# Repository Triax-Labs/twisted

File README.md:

<h1 align="center">Twisted</h1>

Twisted is a tiny (14x32mm to be precise) ESP32-S3 based platform, which has dual Xtensa LX7 cores, 4Mb of flash, 2Mb of PSRAM, 512Kb of SRAM as well as BLE and WiFi on board, paired with an [0.42" IPS LCD](https://www.buydisplay.com/0-42-inch-mini-color-tft-lcd-display-module-96x54-ips-st7735), a keypad, a Neopixel and built-in battery management with USB OTG.

There is one more thing, the platform is extendable! It features a 20 pin 1.27mm expansion header which allows you of attaching other boards that add extra features, giving _Twisted_ a reason for its name.

We currently have three expansion boards for Twisted...

## Twisted Listen

An audio codec based on ES8316, which provides a high performance DAC and ADC, the attachment comes with both a builtin microphone and amplifier for a loudspeaker, as well as a 3.5mm headphone jack (with microphone in.)

## Twisted Connect

A shield for the Twisted Bus that provides the functionality of an extra microcontroller, it adds on a CH585 MCU which comes with an interesting set of peripherals, NFC/RFID (with support for reading, writing and emulating tags,) both a USB High Speed and a USB Full Speed controller as well as a BLE / 2.4GHz modem.

Twisted Connect could be used for using the peripherals on the CH585 MCU alongside the ESP32-S3 on the main Twisted board or it could be used to deep sleep the ESP32-S3 to preserve power, since Twisted Connect could take over the bus, it can wake up the ESP32-S3 when a trigger happens (e.g. sensors over I2C or a BLE/USB packet.)

## Twisted Sense (WIP)

An attachment that provides a a suite of sensors and trackers (pressure, temperature, humidity, gyroscope, accelerometer, magnetometer and GPS/GNSS) aiming to help the device "feel" what happens around it.

## Production

Production could be done through [JLCPCB](https://jlcpcb.com)'s PCBA service.

Total _(estimated)_ costs for Twisted boards (does not include any of the extra shields):

| Item | Price | Qty      | Where                        |
| ---- | ----- | -------- | ---------------------------- |
| PCB  | $7    | 5 Boards | [JLCPCB](https://jlcpcb.com) |
| PCBA | $100  | 5 Boards | [JLCPCB](https://jlcpcb.com) |

You will need to assemble one side of the board, the other side which has the display, a resistor and the keypad you will have to assemble it yourself, or let JLCPCB assemble it for you at a higher cost.

You will need the display to be sourced and assembled by yourself, this is where you can buy it:

- AliExpress: [listing](https://aliexpress.com/item/1005007804650049.html) / [listing](https://aliexpress.com/item/1005008528322628.html) / [listing](https://aliexpress.com/item/1005012246832580.html) / [listing](https://aliexpress.com/item/1005008885821582.html)
- [BuyDisplay](https://www.buydisplay.com/0-42-inch-mini-color-tft-lcd-display-module-96x54-ips-st7735)

If you decide to buy the display from a different supplier, make sure it comes with a 16 pin flex cable, it also has to follow this pinout:

Total _(estimated)_ costs for Twisted Listen boards:

| Item | Price | Qty      | Where                        |
| ---- | ----- | -------- | ---------------------------- |
| PCB  | $7    | 5 Boards | [JLCPCB](https://jlcpcb.com) |
| PCBA | $60   | 5 Boards | [JLCPCB](https://jlcpcb.com) |

Total _(estimated)_ costs for a Twisted Connect boards:

| Item | Price | Qty      | Where                        |
| ---- | ----- | -------- | ---------------------------- |
| PCB  | $7    | 5 Boards | [JLCPCB](https://jlcpcb.com) |
| PCBA | $80   | 5 Boards | [JLCPCB](https://jlcpcb.com) |

_Note that these tables don't include shipping charges._

Production files could be found in `/hardware/X/production`.

## GPIO Pins Mapping (Twisted Bus)

| GPIO | Strap |   ADC    | HWSPI | Remark                                              |      Exposed      | On Twisted        |
| :--: | :---: | :------: | :---: | --------------------------------------------------- | :---------------: | ----------------- |
|  0   |  Yes  |          |       | Pull LOW to Enter BOOT                              |        No         | Boot Button       |
|  1   |  No   | ADC1 CH0 |       |                                                     |        Yes        | Expansion Header  |
|  2   |  No   | ADC1 CH1 |       |                                                     |        Yes        | Expansion Header  |
|  3   |  Yes  | ADC1 CH2 |       | Pull LOW to Use An External Debugger Instead of USB |        Yes        | Expansion Header  |
|  4   |  No   | ADC1 CH3 |       |                                                     |        Yes        | Expansion Header  |
|  5   |  No   | ADC1 CH4 |       |                                                     |        Yes        | Expansion Header  |
|  6   |  No   | ADC1 CH5 |       |                                                     |        Yes        | Expansion Header  |
|  7   |  No   | ADC1 CH6 |       |                                                     |        Yes        | Expansion Header  |
|  8   |  No   | ADC1 CH7 |       |                                                     |        Yes        | Expansion Header  |
|  9   |  No   | ADC1 CH8 | Hold  |                                                     |        Yes        | Expansion Header  |
|  10  |  No   | ADC1 CH9 |  CS   |                                                     |        Yes        | Expansion Header  |
|  11  |  No   | ADC2 CH0 | MOSI  |                                                     |        Yes        | Expansion Header  |
|  12  |  No   | ADC2 CH1 |  SCK  |                                                     |        Yes        | Expansion Header  |
|  13  |  No   | ADC2 CH2 | MISO  |                                                     |        Yes        | Expansion Header  |
|  14  |  No   | ADC2 CH3 |  WP   |                                                     |        Yes        | Expansion Header  |
|  15  |  No   | ADC2 CH4 |       |                                                     |        Yes        | Expansion Header  |
|  16  |  No   | ADC2 CH5 |       |                                                     |        Yes        | Expansion Header  |
|  17  |  No   | ADC2 CH6 |       |                                                     |        Yes        | Expansion Header  |
|  18  |  No   | ADC2 CH7 |       |                                                     |        No         | Keypad: INT       |
|  19  |  Yes  | ADC2 CH8 |       | USB D-                                              |        Yes        | USB Port          |
|  20  |  Yes  | ADC2 CH9 |       | USB D+                                              |        Yes        | USB Port          |
|  21  |  No   |          |       |                                                     |        No         | Neopixel: DIN     |
|  26  |  Yes  |          |       | Used for QSPI Flash/PSRAM                           |        No         | Unused            |
|  27  |  Yes  |          |       | Used for QSPI Flash/PSRAM                           |        No         | Unused            |
|  28  |  Yes  |          |       | Used for QSPI Flash/PSRAM                           |        No         | Unused            |
|  29  |  Yes  |          |       | Used for QSPI Flash/PSRAM                           |        No         | Unused            |
|  30  |  Yes  |          |       | Used for QSPI Flash/PSRAM                           |        No         | Unused            |
|  31  |  Yes  |          |       | Used for QSPI Flash/PSRAM                           |        No         | Unused            |
|  32  |  Yes  |          |       | Used for QSPI Flash/PSRAM                           |        No         | Unused            |
|  33  | Maybe |          |       | Straps for Chips w/ Octal-SPI PSRAM                 |        No         | LCD: RST          |
|  34  | Maybe |          |       | Straps for Chips w/ Octal-SPI PSRAM                 |        No         | LCD: SCK          |
|  35  | Maybe |          |       | Straps for Chips w/ Octal-SPI PSRAM                 |        No         | LCD: CS           |
|  36  | Maybe |          |       | Straps for Chips w/ Octal-SPI PSRAM                 |        No         | LCD: MOSI         |
|  37  | Maybe |          |       | Straps for Chips w/ Octal-SPI PSRAM                 |        No         | LCD: BKL          |
|  38  |  No   |          |       |                                                     |        No         | Unused            |
|  39  |  No   |          |       |                                                     |        No         | Keypad: RST       |
|  40  |  No   |          |       |                                                     |        No         | Unused            |
|  41  |  No   |          |       |                                                     | Through Testpoint | Internal I2C: SDA |
|  42  |  No   |          |       |                                                     | Through Testpoint | Internal I2C: SDA |
|  43  |  No   |          |       | Default UART: TX                                    | Through Testpoint | Unused            |
|  44  |  No   |          |       | Default UART: RX                                    | Through Testpoint | Unused            |
|  45  |  Yes  |          |       |                                                     |        No         | Unused            |
|  46  |  Yes  |          |       |                                                     |        No         | Unused            |
|  47  |  No   |          |       |                                                     |        No         | LCD: DC           |
|  48  |  No   |          |       |                                                     |        No         | BMS: INT          |

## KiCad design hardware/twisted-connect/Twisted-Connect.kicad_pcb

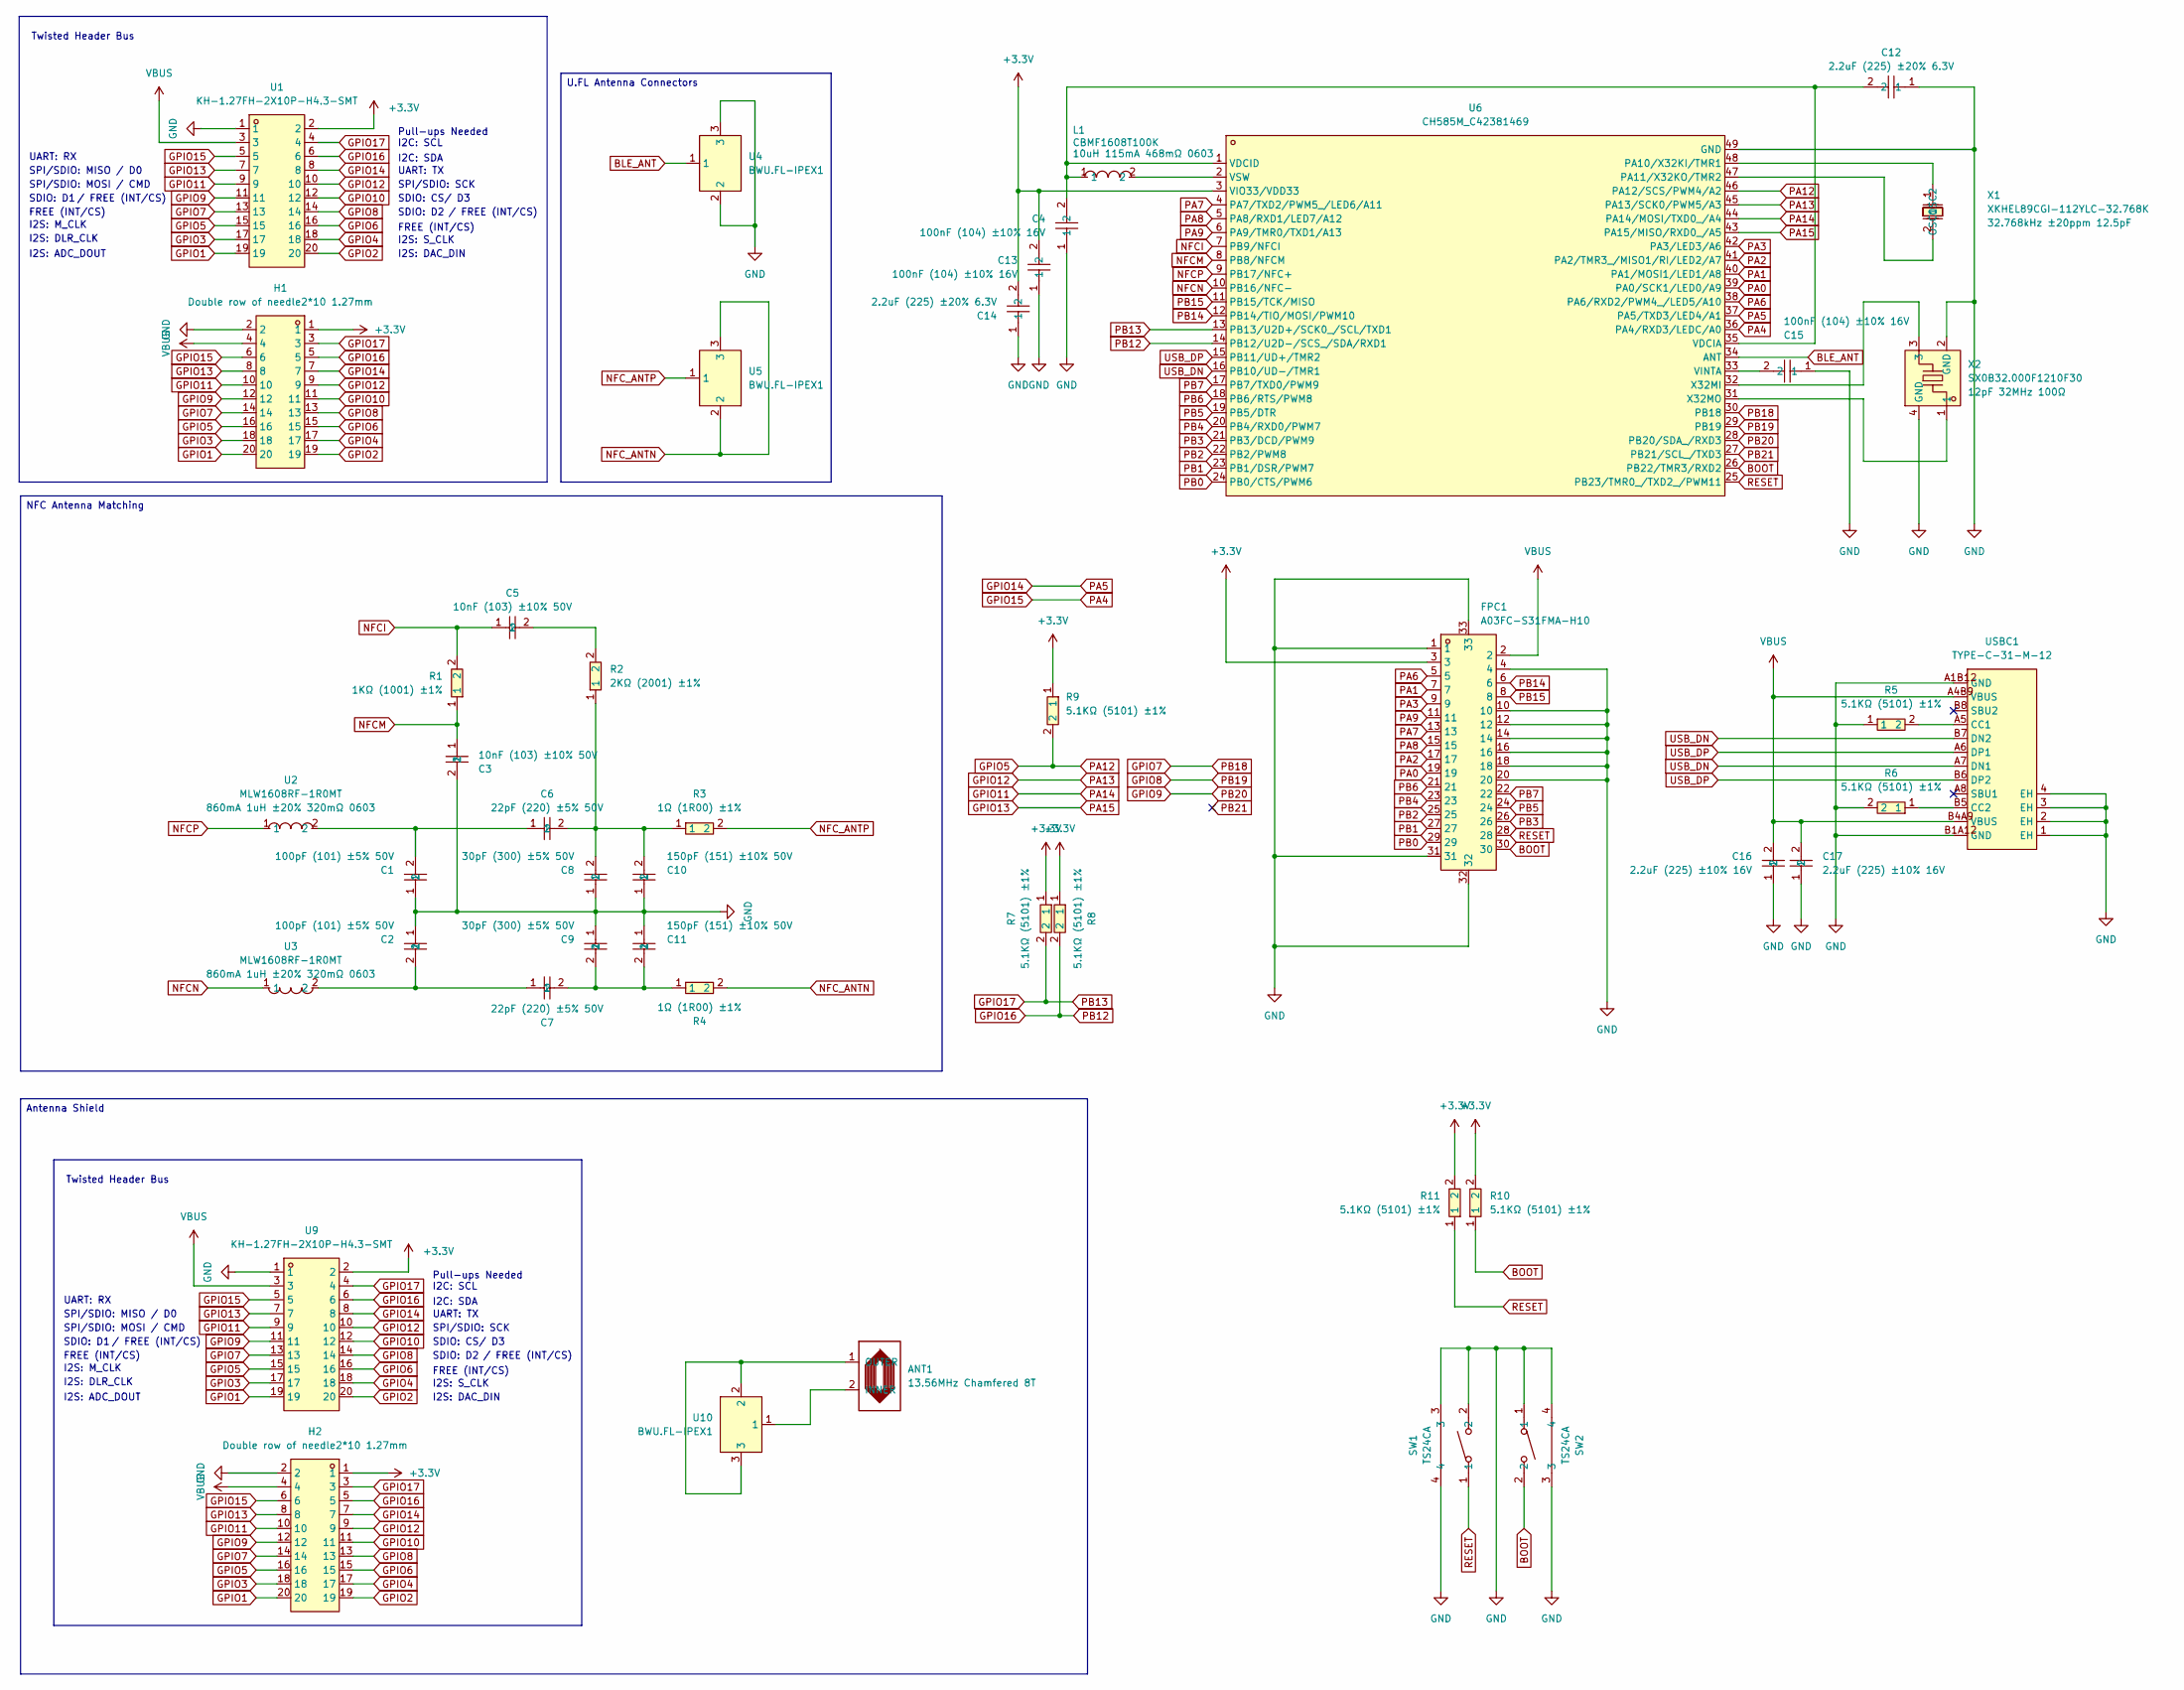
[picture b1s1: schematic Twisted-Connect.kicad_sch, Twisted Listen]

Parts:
ANT1: 13.56MHz Chamfered 8T; Twisted-NFC-Antenna
C1, C2: 0402CG101J500NT; C0402; MPN 0402CG101J500NT; LCSC Part C1546
C3, C5: CL05B103KB5NNNC; C0402; MPN CL05B103KB5NNNC; LCSC Part C15195
C4, C13, C15: CL05B104KO5NNNC; C0402; MPN CL05B104KO5NNNC; LCSC Part C1525
C6, C7: 0402CG220J500NT; C0402; MPN 0402CG220J500NT; LCSC Part C1555
C8, C9: 0402CG300J500NT; C0402; MPN 0402CG300J500NT; LCSC Part C1570
C10, C11: 0402B151K500NT; C0402; MPN 0402B151K500NT; LCSC Part C1527
C12, C14: CL05A225MQ5NSNC; C0402; MPN CL05A225MQ5NSNC; LCSC Part C12530
C16, C17: CL10A225KO8NNNC; C0603; MPN CL10A225KO8NNNC; LCSC Part C23630
FPC1: A03FC-S31FMA-H10; FPC-SMD_31P-P0.60_A03FC-S31FMA-H10; MPN A03FC-S31FMA-H10; LCSC Part C42447807
H1, H2: Double row of needle2*10 1.27mm; HDR-SMD_20P-P1.27-V-M-R2-C10-S1.27-LS5.5-1; MPN 1.27-2*10P立贴针; LCSC Part C59981
L1: CBMF1608T100K; L0603; MPN CBMF1608T100K; LCSC Part C92982
R1: 0402WGF1001TCE; R0402; MPN 0402WGF1001TCE; LCSC Part C11702
R2: 0402WGF2001TCE; R0402; MPN 0402WGF2001TCE; LCSC Part C4109
R3, R4: 0402WGF100KTCE; R0402; MPN 0402WGF100KTCE; LCSC Part C25086
R5, R6, R7, R8, R9, R10, R11: 0402WGF5101TCE; R0402; MPN 0402WGF5101TCE; LCSC Part C25905
SW1, SW2: TS24CA; SW-SMD_2P-TS24CA; MPN TS24CA; LCSC Part C393942
U1, U9: KH-1.27FH-2X10P-H4.3-SMT; CONN-SMD_20P-P1.27_KINGHELM_KH-1.27FH-2X10P-H4.3-SMT; LCSC Part C2938399
U2, U3: MLW1608RF-1R0MT; IND-SMD_L1.8-W1.3; MPN MLW1608RF-1R0MT; LCSC Part C2844624
U4, U5, U10: BWU.FL-IPEX1; IPEX-SMD_BWIPX-1-001E; MPN BWU.FL-IPEX1; LCSC Part C5137195
U6: CH585M_C42381469; QFN-48_L5.0-W5.0-P0.35-TL-EP3.7-1; MPN CH585M; LCSC Part C42381469
USBC1: TYPE-C-31-M-12; USB-C_SMD-TYPE-C-31-M-12_1; MPN TYPE-C-31-M-12; LCSC Part C165948
X1: XKHEL89CGI-112YLC-32.768K; CRYSTAL-SMD_2P-L2.0-W1.2; MPN XKHEL89CGI-112YLC-32.768K; LCSC Part C7500573
X2: SX0B32.000F1210F30; CRYSTAL-SMD_4P-L1.6-W1.2-BL; MPN SX0B32.000F1210F30; LCSC Part C7301923

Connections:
+3.3V: C13.2, C14.2, FPC1.3, H1.1, H2.1, R7.1, R8.1, R9.1, R10.2, R11.2, U1.2, U6.3 (VIO33/VDD33), U9.2
BLE_ANT: U4.1, U6.34 (ANT)
BOOT: FPC1.30, R10.1, SW2.2, U6.26 (PB22/TMR3/RXD2)
GND: C1.1, C2.1, C3.2, C4.1, C8.1, C9.1, C10.1, C11.1, C12.1, C13.1, C14.1, C15.1, C16.1, C17.1, FPC1.1, FPC1.4, FPC1.10, FPC1.12, FPC1.14, FPC1.16, FPC1.18, FPC1.20, FPC1.31, FPC1.32, FPC1.33, H1.2, H2.2, R5.1, R6.2, SW1.2, SW1.3, SW1.4, SW2.1, SW2.3, SW2.4, U1.1, U4.2, U4.3, U6.49 (GND), U9.1, USBC1.1 (EH), USBC1.2 (EH), USBC1.3 (EH), USBC1.4 (EH), USBC1.A1B12 (GND), USBC1.B1A12 (GND), X2.2 (GND), X2.4 (GND)
GPIO1: H1.20, H2.20, U1.19, U9.19
GPIO2: H1.19, H2.19, U1.20, U9.20
GPIO3: H1.18, H2.18, U1.17, U9.17
GPIO4: H1.17, H2.17, U1.18, U9.18
GPIO5: H1.16, H2.16, R9.2, U1.15, U6.46 (PA12/SCS/PWM4/A2), U9.15
GPIO6: H1.15, H2.15, U1.16, U9.16
GPIO7: H1.14, H2.14, U1.13, U6.30 (PB18), U9.13
GPIO8: H1.13, H2.13, U1.14, U6.29 (PB19), U9.14
GPIO9: H1.12, H2.12, U1.11, U6.28 (PB20/SDA_/RXD3), U9.11
GPIO10: H1.11, H2.11, U1.12, U9.12
GPIO11: H1.10, H2.10, U1.9, U6.44 (PA14/MOSI/TXD0_/A4), U9.9
GPIO12: H1.9, H2.9, U1.10, U6.45 (PA13/SCK0/PWM5/A3), U9.10
GPIO13: H1.8, H2.8, U1.7, U6.43 (PA15/MISO/RXD0_/A5), U9.7
GPIO14: H1.7, H2.7, U1.8, U6.37 (PA5/TXD3/LED4/A1), U9.8
GPIO15: H1.6, H2.6, U1.5, U6.36 (PA4/RXD3/LEDC/A0), U9.5
GPIO16: H1.5, H2.5, R8.2, U1.6, U6.14 (PB12/U2D-/SCS_/SDA/RXD1), U9.6
GPIO17: H1.3, H2.3, R7.2, U1.4, U6.13 (PB13/U2D+/SCK0_/SCL/TXD1), U9.4
NFCI: C5.1, R1.2, U6.7 (PB9/NFCI)
NFCM: C3.1, R1.1, U6.8 (PB8/NFCM)
NFCN: U3.1, U6.10 (PB16/NFC-)
NFCP: U2.1, U6.9 (PB17/NFC+)
NFC_ANTN: R4.2, U5.2, U5.3
NFC_ANTP: R3.2, U5.1
unnamed: ANT1.2 (INNER), U10.1
unnamed: ANT1.1 (OUTER), U10.2, U10.3
unnamed: C1.2, C6.1, U2.2
unnamed: C2.2, C7.1, U3.2
unnamed: C5.2, R2.2
unnamed: C6.2, C8.2, C10.2, R2.1, R3.1
unnamed: C7.2, C9.2, C11.2, R4.1
unnamed: U6.48 (PA10/X32KI/TMR1), X1.1 (OSC1)
unnamed: U6.47 (PA11/X32KO/TMR2), X1.2 (OSC2)
unnamed: C4.2, C12.2, L1.1, U6.1 (VDCID), U6.35 (VDCIA)
unnamed: C15.2, U6.33 (VINTA)
unnamed: L1.2, U6.2 (VSW)
unnamed: U6.32 (X32MI), X2.3
unnamed: U6.31 (X32MO), X2.1
unnamed: R5.2, USBC1.A5 (CC1)
unnamed: R6.1, USBC1.B5 (CC2)
PA0: FPC1.19, U6.39 (PA0/SCK1/LED0/A9)
PA1: FPC1.7, U6.40 (PA1/MOSI1/LED1/A8)
PA2: FPC1.17, U6.41 (PA2/TMR3_/MISO1/RI/LED2/A7)
PA3: FPC1.9, U6.42 (PA3/LED3/A6)
PA6: FPC1.5, U6.38 (PA6/RXD2/PWM4_/LED5/A10)
PA7: FPC1.13, U6.4 (PA7/TXD2/PWM5_/LED6/A11)
PA8: FPC1.15, U6.5 (PA8/RXD1/LED7/A12)
PA9: FPC1.11, U6.6 (PA9/TMR0/TXD1/A13)
PB0: FPC1.29, U6.24 (PB0/CTS/PWM6)
PB1: FPC1.27, U6.23 (PB1/DSR/PWM7)
PB2: FPC1.25, U6.22 (PB2/PWM8)
PB3: FPC1.26, U6.21 (PB3/DCD/PWM9)
PB4: FPC1.23, U6.20 (PB4/RXD0/PWM7)
PB5: FPC1.24, U6.19 (PB5/DTR)
PB6: FPC1.21, U6.18 (PB6/RTS/PWM8)
PB7: FPC1.22, U6.17 (PB7/TXD0/PWM9)
PB14: FPC1.6, U6.12 (PB14/TIO/MOSI/PWM10)
PB15: FPC1.8, U6.11 (PB15/TCK/MISO)
PB21: U6.27 (PB21/SCL_/TXD3)
RESET: FPC1.28, R11.1, SW1.1, U6.25 (PB23/TMR0_/TXD2_/PWM11)
USB_DN: U6.16 (PB10/UD-/TMR1), USBC1.A7 (DN1), USBC1.B7 (DN2)
USB_DP: U6.15 (PB11/UD+/TMR2), USBC1.A6 (DP1), USBC1.B6 (DP2)
VBUS: C16.2, C17.2, FPC1.2, H1.4, H2.4, U1.3, U9.3, USBC1.A4B9 (VBUS), USBC1.B4A9 (VBUS)

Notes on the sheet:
SPI/SDIO: MOSI / CMD
FREE (INT/CS)
I2S: DLR_CLK
UART: TX
SDIO: D2
I2S: S_CLK
I2S: ADC_DOUT
Twisted Header Bus
SDIO: CS/ D3
UART: RX
/ FREE (INT/CS)
Pull-ups Needed I2C: SCL
SDIO: D1
SPI/SDIO: SCK
I2C: SDA
I2S: DAC_DIN
SPI/SDIO: MISO / D0
I2S: M_CLK
Antenna Shield
U.FL Antenna Connectors
NFC Antenna Matching

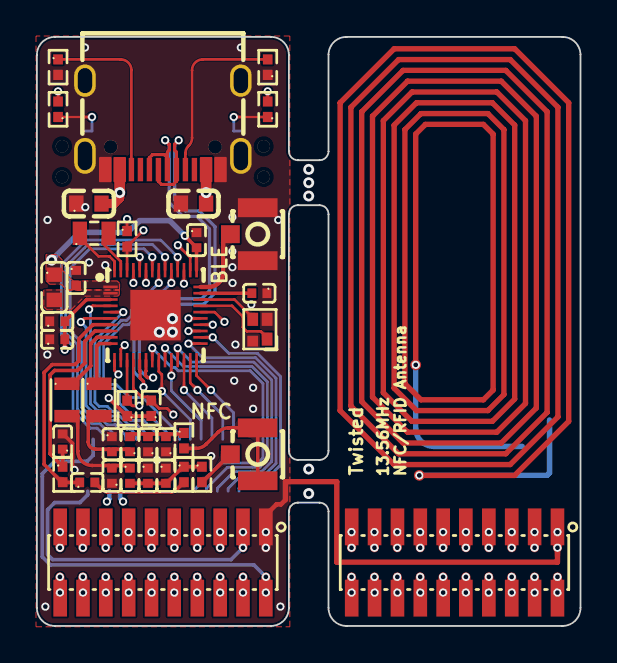
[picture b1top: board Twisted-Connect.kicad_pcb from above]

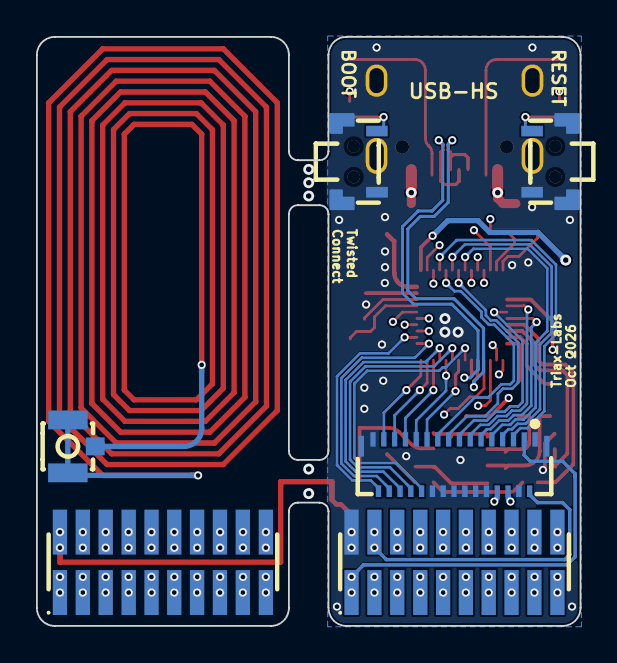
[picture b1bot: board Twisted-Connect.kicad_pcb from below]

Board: 4 copper layers, 30.2 x 32.7 mm, 46 parts (6 on the bottom side), 65 nets.

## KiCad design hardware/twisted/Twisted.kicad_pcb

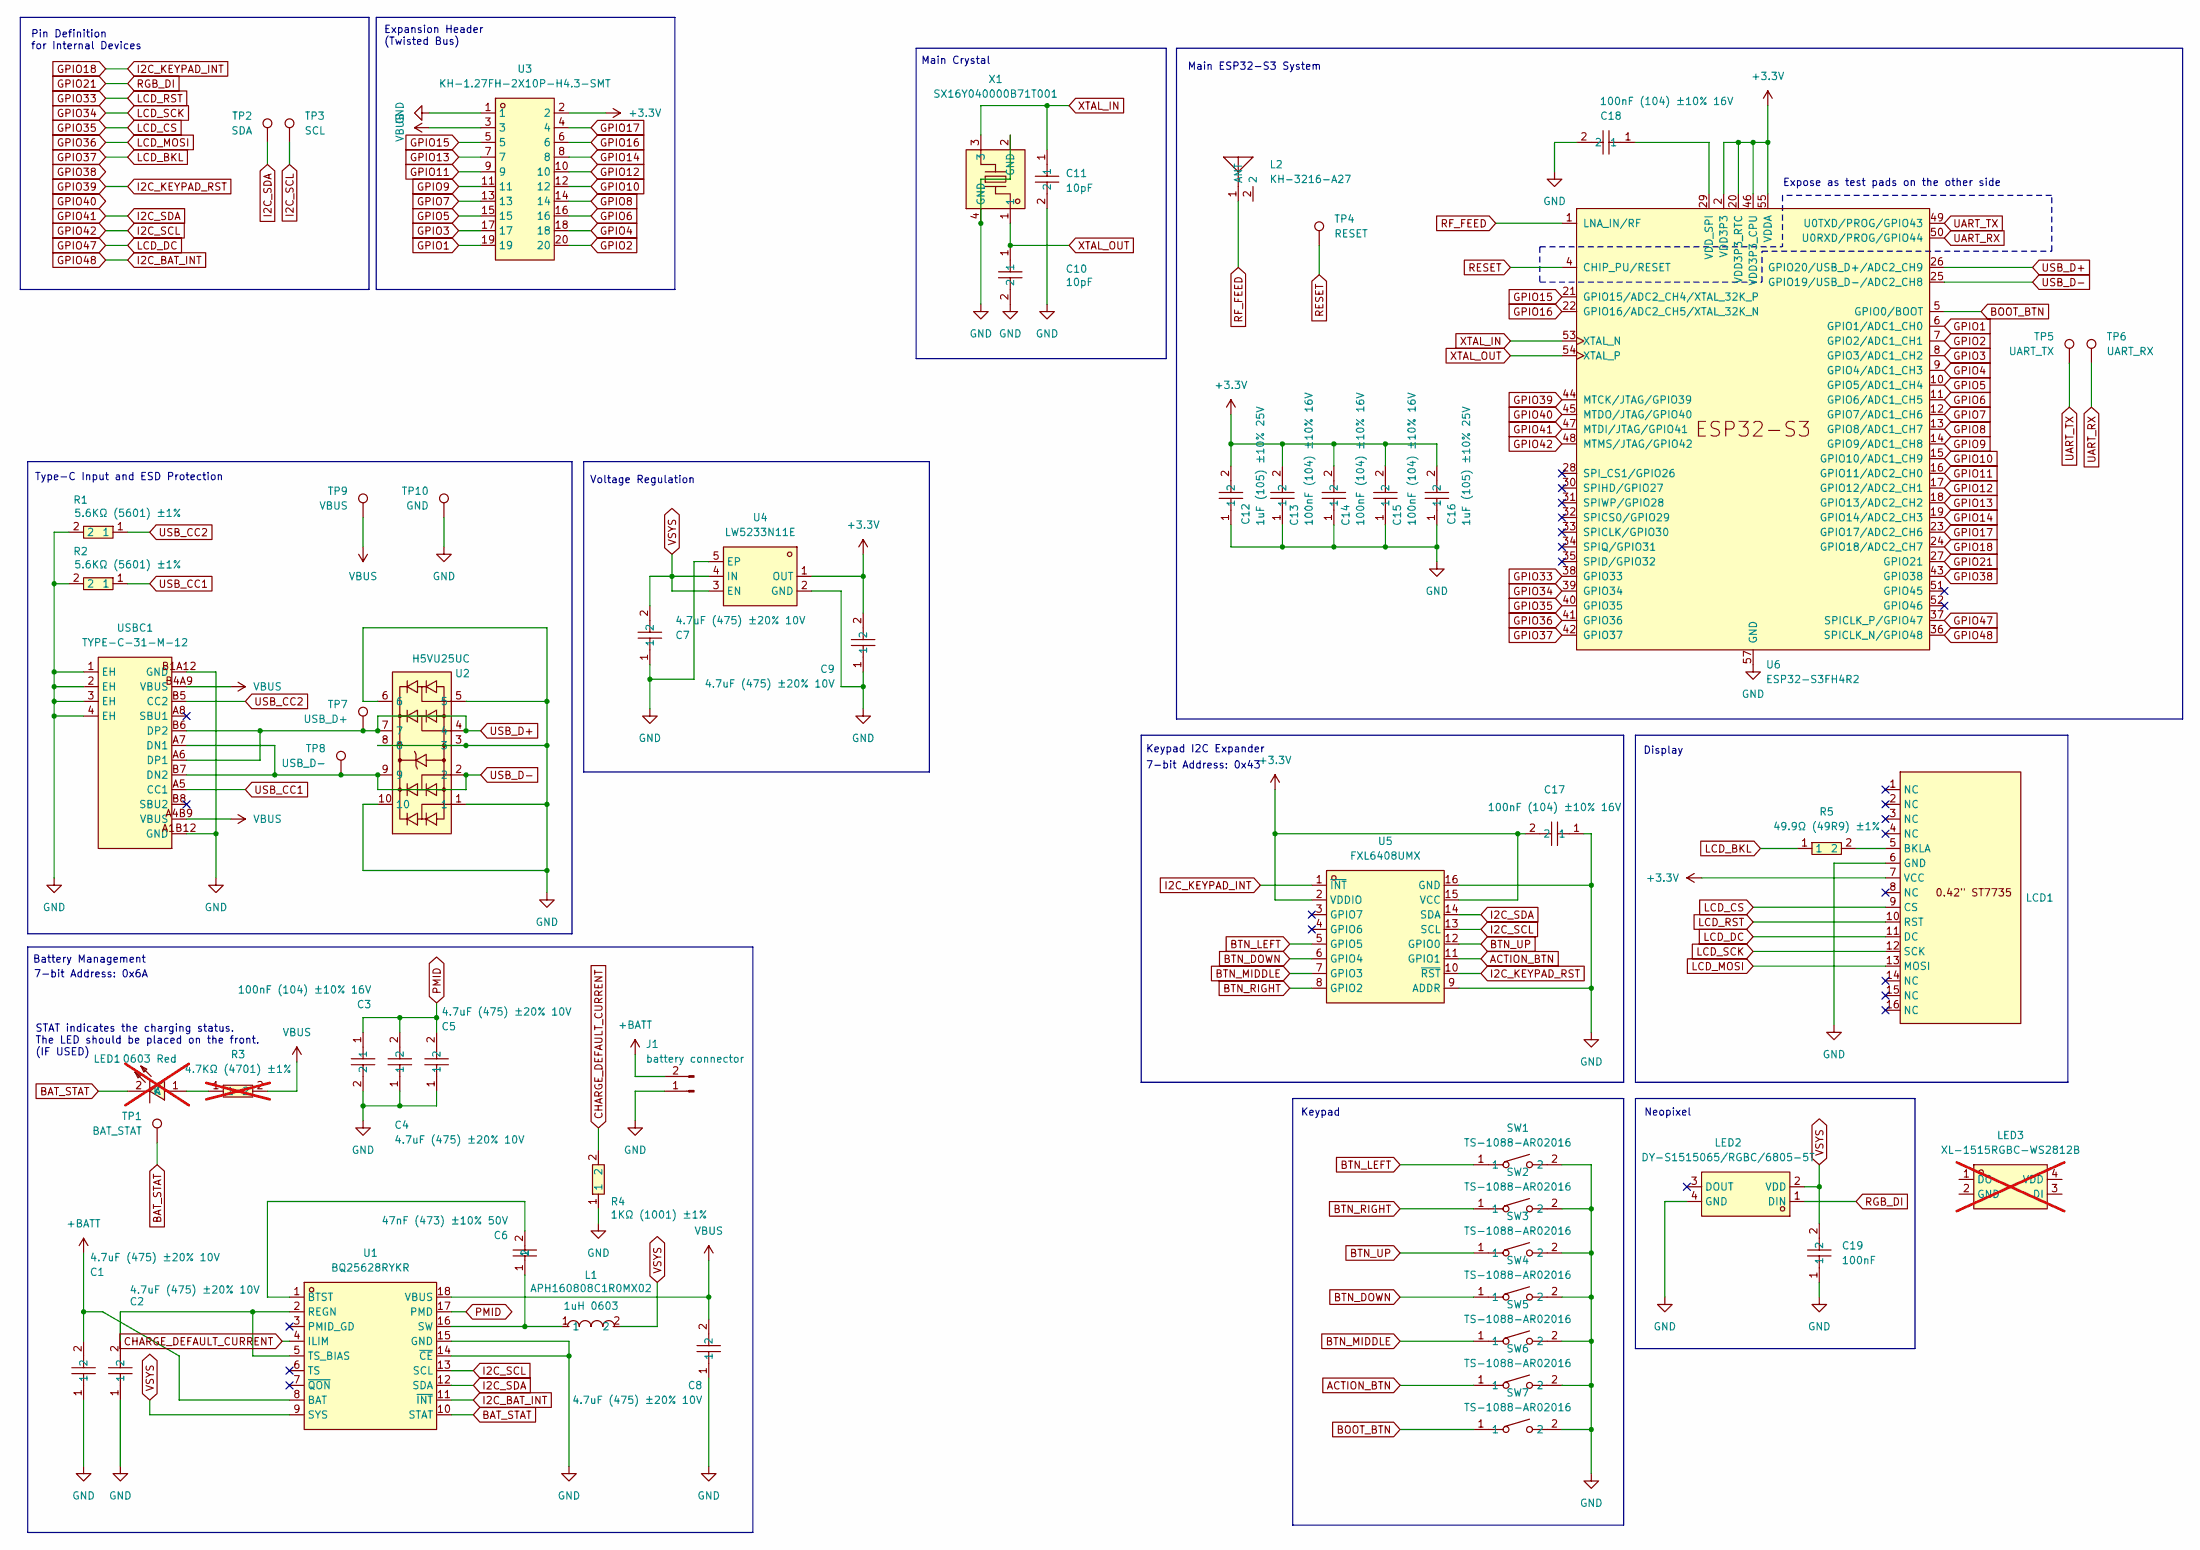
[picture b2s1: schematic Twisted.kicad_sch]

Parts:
C1, C2, C4, C5, C7, C8, C9: CL05A475MP5NRNC; C0402; MPN CL05A475MP5NRNC; LCSC Part C23733
C3, C13, C14, C15, C17, C18: CL05B104KO5NNNC; C0402; MPN CL05B104KO5NNNC; LCSC Part C1525
C6: CL10B473KB8NNNC; C0603; MPN CL10B473KB8NNNC; LCSC Part C1622
C10, C11: CL05C100JB5NNNC; C0402; LCSC Part C32949
C12, C16: CL05A105KA5NQNC; C0402; MPN CL05A105KA5NQNC; LCSC Part C52923
C19: CC0402KRX7R7BB104; C0402; LCSC Part C60474
J1: battery connector; PinSocket_1x02_P1.27mm_Vertical
L1: APH160808C1R0MX02; L0603; MPN APH160808C1R0MP01; LCSC Part C54123751
L2: KH-3216-A27; ANT-SMD_L3.2-W1.6; MPN KH-3216-A27; LCSC Part C504001
LCD1: 0.42-ST7735-Bent
LED1: KT-0603R; LED-SMD_L1.6-W0.8-R-RD; MPN KT-0603R; LCSC Part C2286; not fitted
LED2: DY-S1515065/RGBC/6805-5T; LED-SMD_4P-L1.5-W1.5; MPN DY-S1515065/RGBC/6805-5T; LCSC Part C524053
LED3: XL-1515RGBC-WS2812B; LED-ARRAY-SMD_4P-L1.6-W1.5-P0.85-TL; MPN XL-1515RGBC-2812B; LCSC Part C48586673; not fitted
R1, R2: 0402WGF5601TCE; R0402; MPN 0402WGF5601TCE; LCSC Part C25908
R3: 0402WGF4701TCE; R0402; MPN 0402WGF4701TCE; LCSC Part C25900; not fitted
R4: 0402WGF1001TCE; R0402; MPN 0402WGF1001TCE; LCSC Part C11702
R5: 0402WGF499JTCE; R0402; MPN 0402WGF499JTCE; LCSC Part C25120
SW1, SW2, SW3, SW4, SW5, SW6, SW7: TS-1088-AR02016; SW-SMD_L3.9-W3.0-P4.45; LCSC Part C720477
TP1: BAT_STAT; TinyTestPoint
TP2: SDA; TinyTestPoint
TP3: SCL; TinyTestPoint
TP4: RESET; 2xTinyTestPoint
TP5: UART_TX; 2xTinyTestPoint
TP6: UART_RX; 2xTinyTestPoint
TP7: USB_D+; 2xTinyTestPoint
TP8: USB_D-; 2xTinyTestPoint
TP9: VBUS; 2xTinyTestPoint
TP10: GND; 2xTinyTestPoint
U1: BQ25628RYKR; WQFN-18_L3.0-W2.5-P0.40-TL; MPN BQ25628RYKR; LCSC Part C6055599
U2: H5VU25UC; DFN2510-10_L2.5-W1.0-P0.50-BL; MPN H5VU25UC; LCSC Part C20615800
U3: KH-1.27FH-2X10P-H4.3-SMT; CONN-SMD_20P-P1.27_KINGHELM_KH-1.27FH-2X10P-H4.3-SMT; LCSC Part C2938399
U4: LW5233N11E; DFN-4_L1.0-W1.0-P0.65-BL-EP; MPN LW5233N11E; LCSC Part C20630430
U5: FXL6408UMX; UQFN-16_L2.6-W1.8-P0.40-BL; MPN FXL6408UMX; LCSC Part C457770
U6: ESP32-S3FH4R2; QFN-56_L7.0-W7.0-P0.40-BL-EP5.7; LCSC Part C3013940
USBC1: TYPE-C-31-M-12; USB-C_SMD-TYPE-C-31-M-12_1; LCSC Part C165948
X1: SX16Y040000B71T001; CRYSTAL-SMD_4P-L1.6-W1.2-BL; LCSC Part C20623634

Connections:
+BATT: C1.2, J1.2, U1.8 (BAT)
ACTION_BTN: SW6.1, U5.11 (GPIO1)
BAT_STAT: LED1.2 (K), TP1.1 (1_1), U1.10 (STAT)
BOOT_BTN: SW7.1, U6.5 (GPIO0/BOOT)
BTN_DOWN: SW4.1, U5.6 (GPIO4)
BTN_LEFT: SW1.1, U5.5 (GPIO5)
BTN_MIDDLE: SW5.1, U5.7 (GPIO3)
BTN_RIGHT: SW2.1, U5.8 (GPIO2)
BTN_UP: SW3.1, U5.12 (GPIO0)
CHARGE_DEFAULT_CURRENT: R4.2, U1.4 (ILIM)
GPIO1: U3.19, U6.6 (GPIO1/ADC1_CH0)
GPIO2: U3.20, U6.7 (GPIO2/ADC1_CH1)
GPIO3: U3.17, U6.8 (GPIO3/ADC1_CH2)
GPIO4: U3.18, U6.9 (GPIO4/ADC1_CH3)
GPIO5: U3.15, U6.10 (GPIO5/ADC1_CH4)
GPIO6: U3.16, U6.11 (GPIO6/ADC1_CH5)
GPIO7: U3.13, U6.12 (GPIO7/ADC1_CH6)
GPIO8: U3.14, U6.13 (GPIO8/ADC1_CH7)
GPIO9: U3.11, U6.14 (GPIO9/ADC1_CH8)
GPIO10: U3.12, U6.15 (GPIO10/ADC1_CH9)
GPIO11: U3.9, U6.16 (GPIO11/ADC2_CH0)
GPIO12: U3.10, U6.17 (GPIO12/ADC2_CH1)
GPIO13: U3.7, U6.18 (GPIO13/ADC2_CH2)
GPIO14: U3.8, U6.19 (GPIO14/ADC2_CH3)
GPIO15: U3.5, U6.21 (GPIO15/ADC2_CH4/XTAL_32K_P)
GPIO16: U3.6, U6.22 (GPIO16/ADC2_CH5/XTAL_32K_N)
GPIO17: U3.4, U6.23 (GPIO17/ADC2_CH6)
GPIO18: U5.1 (~INT), U6.24 (GPIO18/ADC2_CH7)
GPIO21: LED2.1 (DIN), U6.27 (GPIO21)
GPIO33: LCD1.10 (RST), U6.38 (GPIO33)
GPIO34: LCD1.12 (SCK), U6.39 (GPIO34)
GPIO35: LCD1.9 (CS), U6.40 (GPIO35)
GPIO36: LCD1.13 (MOSI), U6.41 (GPIO36)
GPIO37: R5.1, U6.42 (GPIO37)
GPIO38: U6.43 (GPIO38)
GPIO39: U5.10 (~RST), U6.44 (MTCK/JTAG/GPIO39)
GPIO40: U6.45 (MTDO/JTAG/GPIO40)
GPIO41: TP2.1 (1_1), U1.12 (SDA), U5.14 (SDA), U6.47 (MTDI/JTAG/GPIO41)
GPIO42: TP3.1 (1_1), U1.13 (SCL), U5.13 (SCL), U6.48 (MTMS/JTAG/GPIO42)
GPIO47: LCD1.11 (DC), U6.37 (SPICLK_P/GPIO47)
GPIO48: U1.11 (~INT), U6.36 (SPICLK_N/GPIO48)
unnamed: LCD1.5 (BKLA), R5.2
unnamed: LED1.1 (A), R3.1
unnamed: C6.2, U1.1 (BTST)
unnamed: C2.2, U1.2 (REGN), U1.5 (TS_BIAS)
unnamed: C6.1, L1.1, U1.16 (SW)
unnamed: C18.1, U6.29 (VDD_SPI)
PMID: C3.1, C4.2, C5.2, U1.17 (PMD)
RESET: TP4.1 (1_1), U6.4 (CHIP_PU/RESET)
RF_FEED: L2.1 (ANT_1), U6.1 (LNA_IN/RF)
UART_RX: TP6.1 (1_1), U6.50 (U0RXD/PROG/GPIO44)
UART_TX: TP5.1 (1_1), U6.49 (U0TXD/PROG/GPIO43)
USB_CC1: R2.1, USBC1.A5 (CC1)
USB_CC2: R1.1, USBC1.B5 (CC2)
USB_D+: TP7.1 (1_1), U2.4, U2.7, U6.26 (GPIO20/USB_D+/ADC2_CH9), USBC1.A6 (DP1), USBC1.B6 (DP2)
USB_D-: TP8.1 (1_1), U2.2, U2.9, U6.25 (GPIO19/USB_D-/ADC2_CH8), USBC1.A7 (DN1), USBC1.B7 (DN2)
VBUS: C8.2, R3.2, TP9.1 (1_1), U1.18 (VBUS), U3.3, USBC1.A4B9 (VBUS), USBC1.B4A9 (VBUS)
VSYS: C7.2, C19.2, L1.2, LED2.2 (VDD), U1.9 (SYS), U4.3 (EN), U4.4 (IN)
XTAL_IN: C11.1, U6.53 (XTAL_N), X1.3

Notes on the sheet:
Main ESP32-S3 System
Expose as test pads on the other side
Neopixel
Keypad I2C Expander
STAT indicates the charging status. The LED should be placed on the front. (IF USED)
Type-C Input and ESD Protection
Battery Management
Main Crystal
Display
Pin Definition for Internal Devices
Expansion Header (Twisted Bus)
Keypad
7-bit Address: 0x43
7-bit Address: 0x6A
Voltage Regulation

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
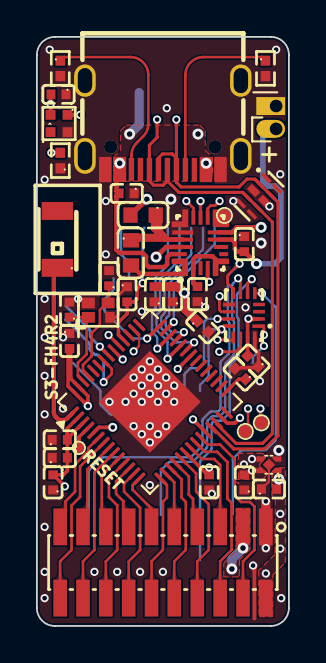
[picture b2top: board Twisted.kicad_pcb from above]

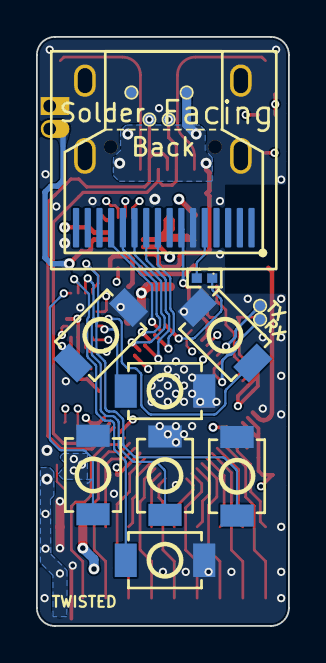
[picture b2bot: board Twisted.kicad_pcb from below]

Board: 4 copper layers, 14.0 x 32.7 mm, 54 parts (15 on the bottom side), 59 nets.

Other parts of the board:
C10#2: CL05C100JB5NNNC; C0402
